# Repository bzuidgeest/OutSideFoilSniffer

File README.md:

This is a PCB design for the outside foil tester as presented and designed by the YouTube channel RestoreOldRadios. I don't like prototyping PCB's so I made a "real" one. I don't do that to often so it's a nice exercise in using Kicad.

Everything seems to be working fine for the smaller value capacitors. but at "larger" values the detected signal gets to low for the Arduino to measure. And larger is 0.1uF and more. Also I found that capacitors with the cardboard tubes and the modern yellow ones test fine. But I also have vintage ones using a plastic tube as a housing. That type also doesn't measure. Might be that the plastic is to much of an insulator

Some Obligatory pictures:

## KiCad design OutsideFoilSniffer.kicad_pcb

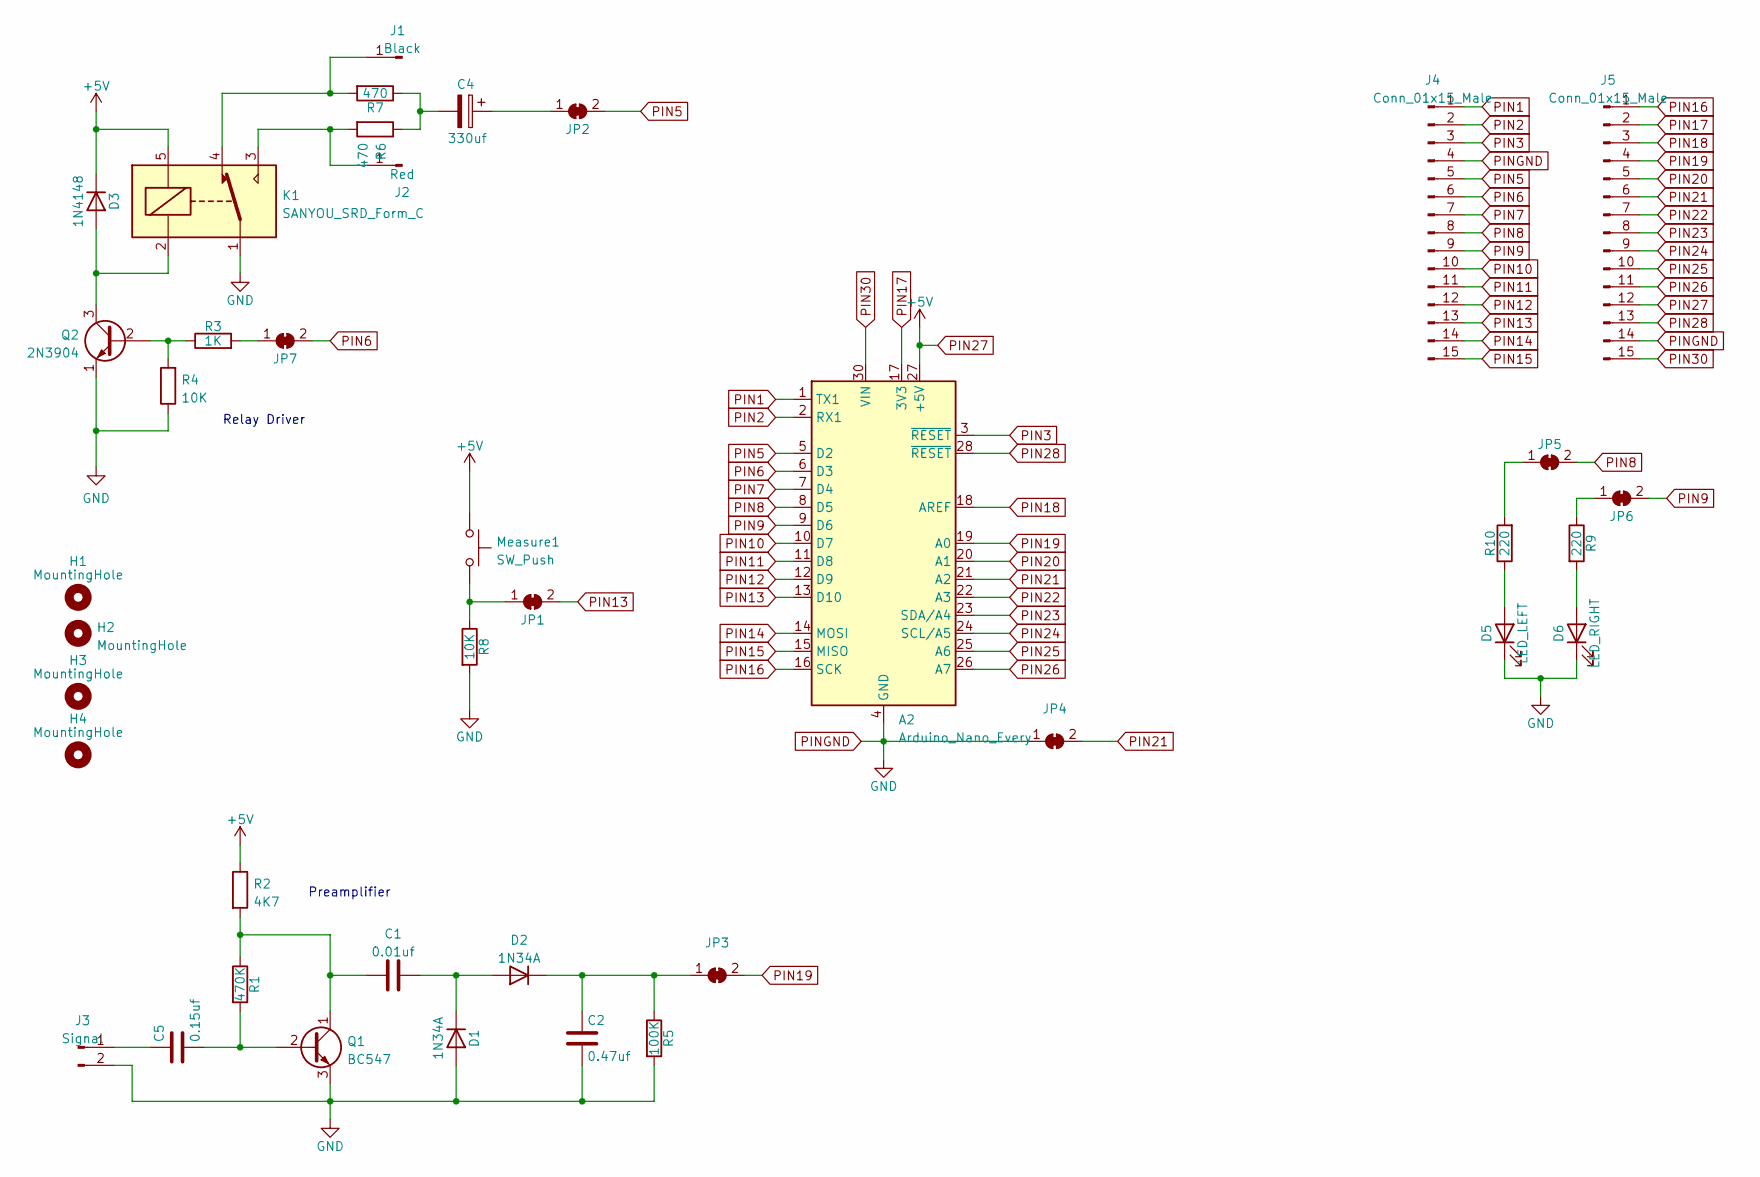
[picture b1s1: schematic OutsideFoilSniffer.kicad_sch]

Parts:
A2: Arduino_Nano_Every; Arduino_Nano
C1: 0.01uf; C_Rect_L10.0mm_W3.0mm_P7.50mm_MKS4
C2: 0.47uf; C_Rect_L7.0mm_W2.5mm_P5.00mm
C4: 330uf; CP_Radial_D8.0mm_P5.00mm
C5: 0.15uf; C_Rect_L13.0mm_W4.0mm_P10.00mm_FKS3_FKP3_MKS4
D1, D2: 1N34A; D_DO-35_SOD27_P10.16mm_Horizontal
D3: 1N4148; D_DO-35_SOD27_P7.62mm_Horizontal
D5: LED_LEFT; LED_D5.0mm
D6: LED_RIGHT; LED_D5.0mm
H1, H2, H3, H4: MountingHole; MountingHole_3.2mm_M3
J1: Black; Banana_Jack_1Pin
J2: Red; Banana_Jack_1Pin
J3: Signal; SMA_Amphenol_901-144_Vertical
J4, J5: Conn_01x15_Male; PinHeader_1x15_P2.54mm_Vertical
JP1, JP2, JP3, JP4, JP5, JP6, JP7: SolderJumper-2_P1.3mm_Bridged_Pad1.0x1.5mm
K1: SANYOU_SRD_Form_C; Relay_SPDT_SANYOU_SRD_Series_Form_C
Measure1: SW_Push; SW_PUSH_6mm
Q1: BC547; TO-92_Inline_Wide
Q2: 2N3904; TO-92_Inline_Wide
R1: 470K; R_Axial_DIN0207_L6.3mm_D2.5mm_P10.16mm_Horizontal
R2: 4K7; R_Axial_DIN0207_L6.3mm_D2.5mm_P10.16mm_Horizontal
R3: 1K; R_Axial_DIN0207_L6.3mm_D2.5mm_P10.16mm_Horizontal
R4, R8: 10K; R_Axial_DIN0207_L6.3mm_D2.5mm_P10.16mm_Horizontal
R5: 100K; R_Axial_DIN0207_L6.3mm_D2.5mm_P10.16mm_Horizontal
R6, R7: 470; R_Axial_DIN0207_L6.3mm_D2.5mm_P10.16mm_Horizontal
R9, R10: 220; R_Axial_DIN0207_L6.3mm_D2.5mm_P10.16mm_Horizontal

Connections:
unnamed: C1.1, D1.1 (K), D2.2 (A)
unnamed: C1.2, Q1.1 (C), R1.1, R2.2
unnamed: C2.1, D2.1 (K), JP3.1 (A), R5.1
unnamed: C4.1, JP2.1 (A)
unnamed: C4.2, R6.1, R7.1
unnamed: C5.1, J3.1
unnamed: C5.2, Q1.2 (B), R1.2
unnamed: D3.2 (A), K1.2, Q2.3 (C)
unnamed: D5.2 (A), R10.1
unnamed: D6.2 (A), R9.2
unnamed: J1.1, K1.4, R7.2
unnamed: J2.1, K1.3, R6.2
unnamed: JP1.1 (A), Measure1.2, R8.1
unnamed: JP5.1 (A), R10.2
unnamed: JP6.1 (A), R9.1
unnamed: JP7.1 (A), R3.2
unnamed: Q2.2 (B), R3.1, R4.2
PIN1: A2.1 (TX1), J4.1
PIN2: A2.2 (RX1), J4.2
PIN3: A2.3 (~RESET), J4.3
PIN5: A2.5 (D2), J4.5, JP2.2 (B)
PIN6: A2.6 (D3), J4.6, JP7.2 (B)
PIN7: A2.7 (D4), J4.7
PIN8: A2.8 (D5), J4.8, JP5.2 (B)
PIN9: A2.9 (D6), J4.9, JP6.2 (B)
PIN10: A2.10 (D7), J4.10
PIN11: A2.11 (D8), J4.11
PIN12: A2.12 (D9), J4.12
PIN13: A2.13 (D10), J4.13, JP1.2 (B)
PIN14: A2.14 (MOSI), J4.14
PIN15: A2.15 (MISO), J4.15
PIN16: A2.16 (SCK), J5.1
PIN17: A2.17 (3V3), J5.2
PIN18: A2.18 (AREF), J5.3
PIN19: A2.19 (A0), J5.4, JP3.2 (B)
PIN20: A2.20 (A1), J5.5
PIN21: A2.21 (A2), J5.6, JP4.2 (B)
PIN22: A2.22 (A3), J5.7
PIN23: A2.23 (SDA/A4), J5.8
PIN24: A2.24 (SCL/A5), J5.9
PIN25: A2.25 (A6), J5.10
PIN26: A2.26 (A7), J5.11
PIN27: A2.27 (+5V), D3.1 (K), J5.12, K1.5, Measure1.1, R2.1
PIN28: A2.28 (~RESET), J5.13
PIN30: A2.30 (VIN), J5.15
PINGND: A2.4 (GND), A2.29 (GND), C2.2, D1.2 (A), D5.1 (K), D6.1 (K), J3.2, J4.4, J5.14, JP4.1 (A), K1.1, Q1.3 (E), Q2.1 (E), R4.1, R5.2, R8.2

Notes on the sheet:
Preamplifier
Relay Driver

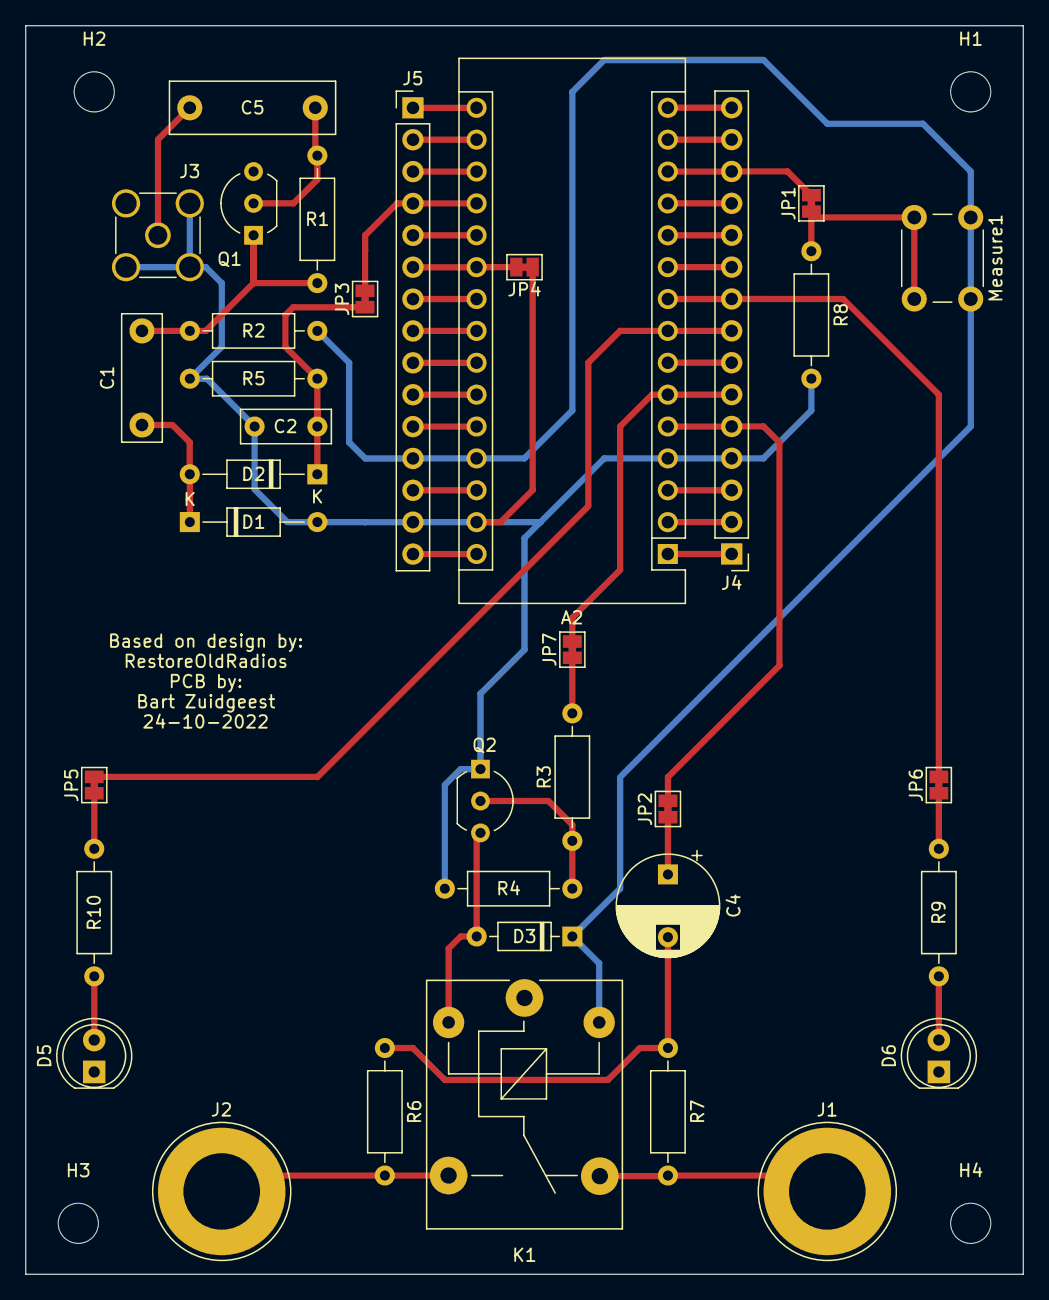
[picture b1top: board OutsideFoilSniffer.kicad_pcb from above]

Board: 2 copper layers, 79.5 x 99.5 mm, 40 parts (0 on the bottom side), 46 nets.

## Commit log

2022-10-12 first draft, need to check package sizes
2022-10-12 added readme
2022-10-24 Modified size to fit PCBWay prototype size 100x80 mm for cheap price
2022-10-24 minor changes
2022-10-29 Added sniffer code modified for my design. Code needs serious cleanup
2022-10-29 Code clean-up much more clean now. Seems to still work on the breadboard.
2022-11-13 small enhancements and a picture
2022-11-13 Update README.md
    add some more explenation and results and images
2024-06-23 Fix to code, now we have output when one of the leads reads zero
